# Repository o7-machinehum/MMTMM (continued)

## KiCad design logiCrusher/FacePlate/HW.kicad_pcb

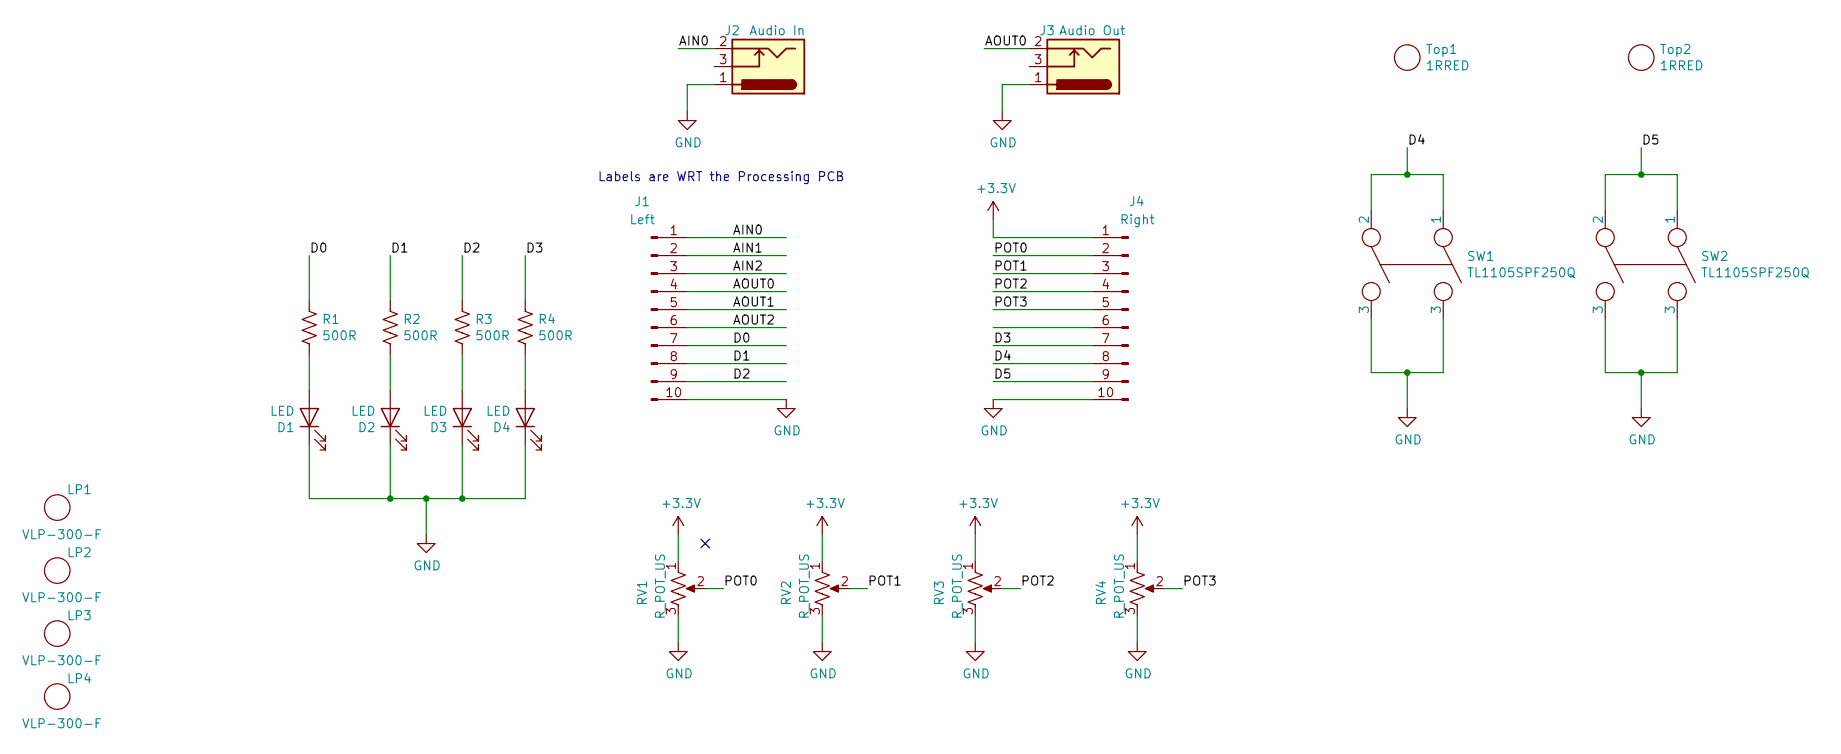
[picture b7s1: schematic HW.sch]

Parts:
D1, D2, D3, D4: LED; LED_0805_2012Metric
J1: Left; PinHeader_1x10_P2.54mm_Vertical
J2: Audio In; PJ301M-12
J3: Audio Out; PJ301M-12
J4: Right; PinHeader_1x10_P2.54mm_Vertical
LP1, LP2, LP3, LP4: VLP-300-F
R1, R2, R3, R4: 500R; R_0805_2012Metric
RV1, RV2, RV3, RV4: R_POT_US; Alpha9mmPot
SW1, SW2: TL1105SPF250Q
Top1, Top2: 1RRED

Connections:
+3V3: J4.1, RV1.1, RV2.1, RV3.1, RV4.1
/AIN0: J1.1, J2.2
/AIN1: J1.2
/AIN2: J1.3
/AOUT0: J1.4, J3.2
/AOUT1: J1.5
/AOUT2: J1.6
/D0: J1.7, R1.1
/D1: J1.8, R2.1
/D2: J1.9, R3.1
/D3: J4.7, R4.1
/D4: J4.8, SW1.1, SW1.2
/D5: J4.9, SW2.1, SW2.2
/POT0: J4.2, RV1.2
/POT1: J4.3, RV2.2
/POT2: J4.4, RV3.2
/POT3: J4.5, RV4.2
GND: D1.1 (K), D2.1 (K), D3.1 (K), D4.1 (K), J1.10, J2.1, J3.1, J4.10, RV1.3, RV2.3, RV3.3, RV4.3, SW1.3, SW2.3
unnamed: D1.2 (A), R1.2
unnamed: D2.2 (A), R2.2
unnamed: D3.2 (A), R3.2
unnamed: D4.2 (A), R4.2

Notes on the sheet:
Labels are WRT the Processing PCB

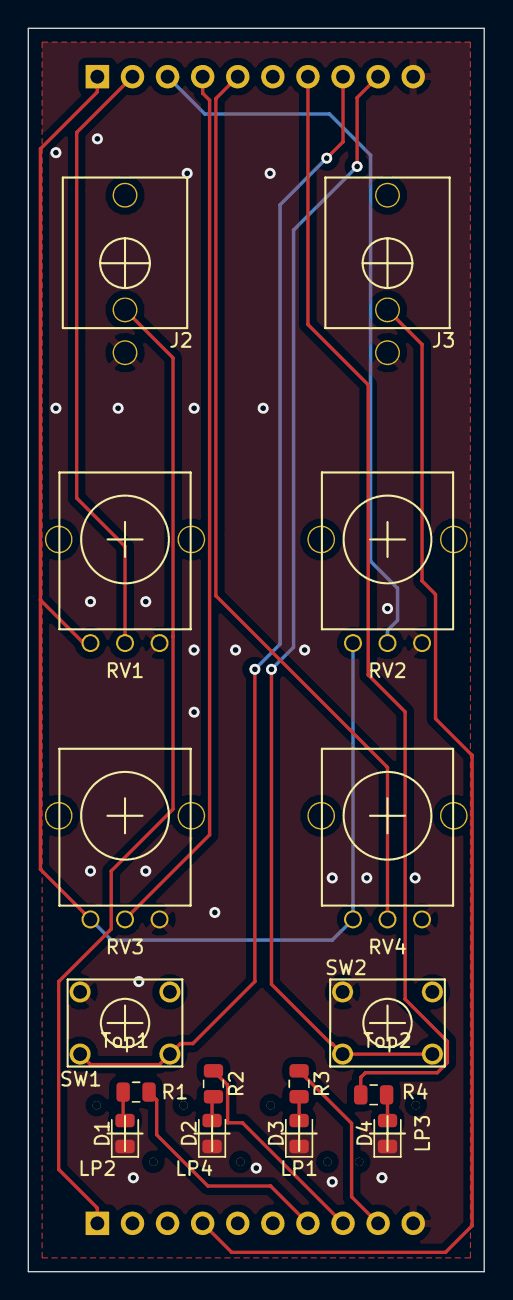
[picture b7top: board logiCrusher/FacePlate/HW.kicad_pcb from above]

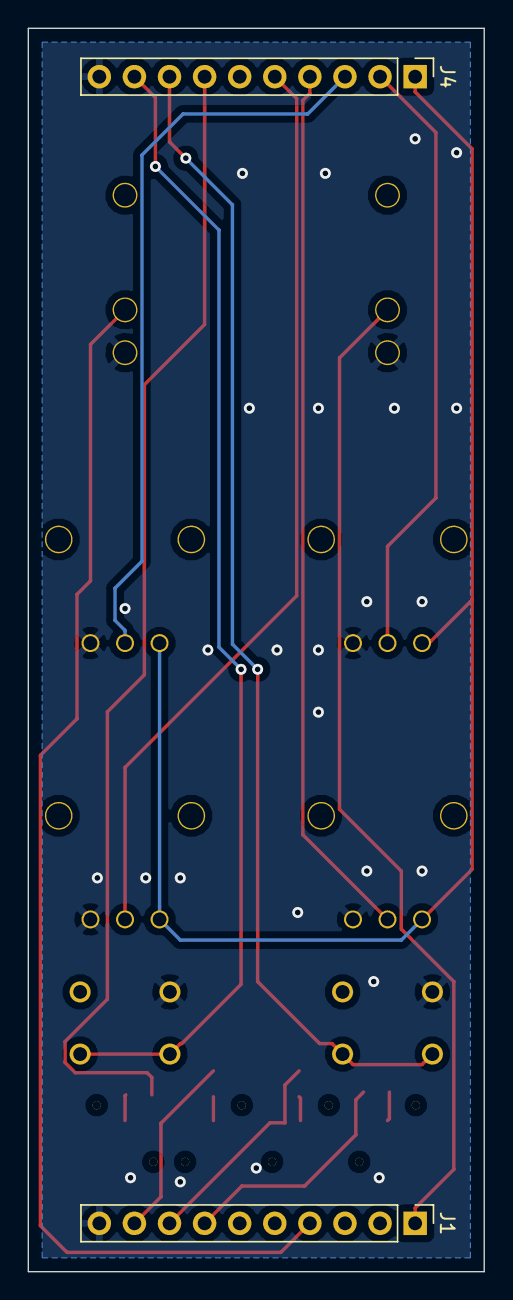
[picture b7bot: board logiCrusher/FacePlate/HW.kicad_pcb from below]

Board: 2 copper layers, 33.0 x 90.0 mm, 24 parts (2 on the bottom side), 18 nets.

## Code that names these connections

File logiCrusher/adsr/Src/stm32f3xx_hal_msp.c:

#include "main.h"
extern DMA_HandleTypeDef hdma_adc1;
void HAL_MspInit(void)
{
  /* USER CODE BEGIN MspInit 0 */

  /* USER CODE END MspInit 0 */

  __HAL_RCC_SYSCFG_CLK_ENABLE();
  __HAL_RCC_PWR_CLK_ENABLE();

  /* System interrupt init*/
  /* PendSV_IRQn interrupt configuration */
  HAL_NVIC_SetPriority(PendSV_IRQn, 15, 0);

  /* USER CODE BEGIN MspInit 1 */

  /* USER CODE END MspInit 1 */
}

/**
* @brief ADC MSP Initialization
* This function configures the hardware resources used in this example
* @param hadc: ADC handle pointer
* @retval None
*/
void HAL_ADC_MspInit(ADC_HandleTypeDef* hadc)
{
  GPIO_InitTypeDef GPIO_InitStruct = {0};
  if(hadc->Instance==ADC1)
  {
  /* USER CODE BEGIN ADC1_MspInit 0 */

  /* USER CODE END ADC1_MspInit 0 */
    /* Peripheral clock enable */
    __HAL_RCC_ADC1_CLK_ENABLE();
  
    __HAL_RCC_GPIOA_CLK_ENABLE();
    /**ADC1 GPIO Configuration    
    PA0     ------> ADC1_IN0
    PA1     ------> ADC1_IN1
    PA2     ------> ADC1_IN2
    PA3     ------> ADC1_IN3 
    */
    GPIO_InitStruct.Pin = GPIO_PIN_0|GPIO_PIN_1|GPIO_PIN_2|GPIO_PIN_3;
    GPIO_InitStruct.Mode = GPIO_MODE_ANALOG;
    GPIO_InitStruct.Pull = GPIO_NOPULL;
    HAL_GPIO_Init(GPIOA, &GPIO_InitStruct);

  }

}

/**
* @brief ADC MSP De-Initialization
* This function freeze the hardware resources used in this example
* @param hadc: ADC handle pointer
* @retval None
*/
void HAL_ADC_MspDeInit(ADC_HandleTypeDef* hadc)
{
  if(hadc->Instance==ADC1)
  {
  /* USER CODE BEGIN ADC1_MspDeInit 0 */

  /* USER CODE END ADC1_MspDeInit 0 */
    /* Peripheral clock disable */
    __HAL_RCC_ADC1_CLK_DISABLE();
  
    /**ADC1 GPIO Configuration    
    PA0     ------> ADC1_IN0
    PA1     ------> ADC1_IN1
    PA2     ------> ADC1_IN2
    PA3     ------> ADC1_IN3 
    */
    HAL_GPIO_DeInit(GPIOA, GPIO_PIN_0|GPIO_PIN_1|GPIO_PIN_2|GPIO_PIN_3);

    /* ADC1 DMA DeInit */
    HAL_DMA_DeInit(hadc->DMA_Handle);
  /* USER CODE BEGIN ADC1_MspDeInit 1 */

  /* USER CODE END ADC1_MspDeInit 1 */
  }

}

/**
* @brief DAC MSP Initialization
* This function configures the hardware resources used in this example
* @param hdac: DAC handle pointer
* @retval None
*/
void HAL_DAC_MspInit(DAC_HandleTypeDef* hdac)
{
  GPIO_InitTypeDef GPIO_InitStruct = {0};
  if(hdac->Instance==DAC1)
  {
  /* USER CODE BEGIN DAC1_MspInit 0 */

  /* USER CODE END DAC1_MspInit 0 */
    /* Peripheral clock enable */
    __HAL_RCC_DAC1_CLK_ENABLE();
  
    __HAL_RCC_GPIOA_CLK_ENABLE();
    /**DAC1 GPIO Configuration    
    PA4     ------> DAC1_OUT1 
    */
    GPIO_InitStruct.Pin = GPIO_PIN_4;
    GPIO_InitStruct.Mode = GPIO_MODE_ANALOG;
    GPIO_InitStruct.Pull = GPIO_NOPULL;
    HAL_GPIO_Init(GPIOA, &GPIO_InitStruct);

  /* USER CODE BEGIN DAC1_MspInit 1 */

  /* USER CODE END DAC1_MspInit 1 */
  }
  else if(hdac->Instance==DAC2)
  {
  /* USER CODE BEGIN DAC2_MspInit 0 */

  /* USER CODE END DAC2_MspInit 0 */
    /* Peripheral clock enable */
    __HAL_RCC_DAC2_CLK_ENABLE();
  
    __HAL_RCC_GPIOA_CLK_ENABLE();
    /**DAC2 GPIO Configuration    
    PA6     ------> DAC2_OUT1 
    */
    GPIO_InitStruct.Pin = GPIO_PIN_6;
    GPIO_InitStruct.Mode = GPIO_MODE_ANALOG;
    GPIO_InitStruct.Pull = GPIO_NOPULL;
    HAL_GPIO_Init(GPIOA, &GPIO_InitStruct);

  /* USER CODE BEGIN DAC2_MspInit 1 */

  /* USER CODE END DAC2_MspInit 1 */
  }

}

/**
* @brief DAC MSP De-Initialization
* This function freeze the hardware resources used in this example
* @param hdac: DAC handle pointer
* @retval None
*/
void HAL_DAC_MspDeInit(DAC_HandleTypeDef* hdac)
{
  if(hdac->Instance==DAC1)
  {
  /* USER CODE BEGIN DAC1_MspDeInit 0 */

  /* USER CODE END DAC1_MspDeInit 0 */
    /* Peripheral clock disable */
    __HAL_RCC_DAC1_CLK_DISABLE();
  
    /**DAC1 GPIO Configuration    
    PA4     ------> DAC1_OUT1 
    */
    HAL_GPIO_DeInit(GPIOA, GPIO_PIN_4);

  /* USER CODE BEGIN DAC1_MspDeInit 1 */

  /* USER CODE END DAC1_MspDeInit 1 */
  }
  else if(hdac->Instance==DAC2)
  {
  /* USER CODE BEGIN DAC2_MspDeInit 0 */

  /* USER CODE END DAC2_MspDeInit 0 */
    /* Peripheral clock disable */
    __HAL_RCC_DAC2_CLK_DISABLE();
  
    /**DAC2 GPIO Configuration    
    PA6     ------> DAC2_OUT1 
    */
    HAL_GPIO_DeInit(GPIOA, GPIO_PIN_6);

  /* USER CODE BEGIN DAC2_MspDeInit 1 */

  /* USER CODE END DAC2_MspDeInit 1 */
  }

}

/**
* @brief SDADC MSP Initialization
* This function configures the hardware resources used in this example
* @param hsdadc: SDADC handle pointer
* @retval None
*/
void HAL_SDADC_MspInit(SDADC_HandleTypeDef* hsdadc)
{
  GPIO_InitTypeDef GPIO_InitStruct = {0};
  if(hsdadc->Instance==SDADC1)
  {
    /* Peripheral clock enable */
    __HAL_RCC_SDADC1_CLK_ENABLE();
    __HAL_RCC_GPIOB_CLK_ENABLE();
    /**SDADC1 GPIO Configuration    
    PB2     ------> SDADC1_AIN4P 
    */
    GPIO_InitStruct.Pin = GPIO_PIN_2;
    GPIO_InitStruct.Mode = GPIO_MODE_ANALOG;
    GPIO_InitStruct.Pull = GPIO_NOPULL;
    HAL_GPIO_Init(GPIOB, &GPIO_InitStruct);
    
    HAL_NVIC_SetPriority(SDADC1_IRQn, 5, 0);
    HAL_NVIC_EnableIRQ(SDADC1_IRQn);
  }
}

/**
* @brief SDADC MSP De-Initialization
* This function freeze the hardware resources used in this example
* @param hsdadc: SDADC handle pointer
* @retval None
*/
void HAL_SDADC_MspDeInit(SDADC_HandleTypeDef* hsdadc)
{
  if(hsdadc->Instance==SDADC1)
  {
  /* USER CODE BEGIN SDADC1_MspDeInit 0 */

  /* USER CODE END SDADC1_MspDeInit 0 */
    /* Peripheral clock disable */
    __HAL_RCC_SDADC1_CLK_DISABLE();
  
    /**SDADC1 GPIO Configuration    
    PB2     ------> SDADC1_AIN4P 
    */
    HAL_GPIO_DeInit(GPIOB, GPIO_PIN_2);

  /* USER CODE BEGIN SDADC1_MspDeInit 1 */

  /* USER CODE END SDADC1_MspDeInit 1 */
  }

}

/**
* @brief UART MSP Initialization
* This function configures the hardware resources used in this example
* @param huart: UART handle pointer
* @retval None
*/
void HAL_UART_MspInit(UART_HandleTypeDef* huart)
{
  GPIO_InitTypeDef GPIO_InitStruct = {0};
  if(huart->Instance==USART2)
  {
  /* USER CODE BEGIN USART2_MspInit 0 */

  /* USER CODE END USART2_MspInit 0 */
    /* Peripheral clock enable */
    __HAL_RCC_USART2_CLK_ENABLE();
  
    __HAL_RCC_GPIOB_CLK_ENABLE();
    /**USART2 GPIO Configuration    
    PB3     ------> USART2_TX
    PB4     ------> USART2_RX 
    */
    GPIO_InitStruct.Pin = GPIO_PIN_3|GPIO_PIN_4;
    GPIO_InitStruct.Mode = GPIO_MODE_AF_PP;
    GPIO_InitStruct.Pull = GPIO_NOPULL;
    GPIO_InitStruct.Speed = GPIO_SPEED_FREQ_HIGH;
    GPIO_InitStruct.Alternate = GPIO_AF7_USART2;
    HAL_GPIO_Init(GPIOB, &GPIO_InitStruct);

    /* USART2 interrupt Init */
    HAL_NVIC_SetPriority(USART2_IRQn, 5, 0);
    HAL_NVIC_EnableIRQ(USART2_IRQn);
  /* USER CODE BEGIN USART2_MspInit 1 */

  /* USER CODE END USART2_MspInit 1 */
  }

}

/**
* @brief UART MSP De-Initialization
* This function freeze the hardware resources used in this example
* @param huart: UART handle pointer
* @retval None
*/
void HAL_UART_MspDeInit(UART_HandleTypeDef* huart)
{
  if(huart->Instance==USART2)
  {
  /* USER CODE BEGIN USART2_MspDeInit 0 */

  /* USER CODE END USART2_MspDeInit 0 */
    /* Peripheral clock disable */
    __HAL_RCC_USART2_CLK_DISABLE();
  
    /**USART2 GPIO Configuration    
    PB3     ------> USART2_TX
    PB4     ------> USART2_RX 
    */
    HAL_GPIO_DeInit(GPIOB, GPIO_PIN_3|GPIO_PIN_4);

    /* USART2 interrupt DeInit */
    HAL_NVIC_DisableIRQ(USART2_IRQn);
  /* USER CODE BEGIN USART2_MspDeInit 1 */

  /* USER CODE END USART2_MspDeInit 1 */
  }

}

/* USER CODE BEGIN 1 */

/* USER CODE END 1 */

/************************ (C) COPYRIGHT STMicroelectronics *****END OF FILE****/

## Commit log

2018-09-25 init
2018-09-25 Added kicad files for VCO front plate.
2018-10-03 Updated the readme
2018-11-07 Added Altium files for front plate.
2018-11-08 Renders done for VCO front plate.
2018-11-09 Added front files for for LFO
2018-12-04 Changed the readme
2018-12-25 Cleaned up the spec for VCM
2018-12-25 Typo
2018-12-25 Added some parts
2018-12-25 Added some notes in the spec
2018-12-27 Added another MCU
2018-12-27 Added some kicad files
2018-12-27 Added power headers and some caps for the pcb.
2018-12-29 Moved some shit around, changed the spec, worked on the PCB
2019-01-03 Worked on the PCB
2019-01-04 Routed some of the lines in.
2019-01-08 Added buffer parts
2019-02-28 Finished the first crack at the drum module
2019-03-08 Finished ASDR schematic.
2019-03-24 Made FW for the logiCrusher
2019-03-24 Going to generate cube stuff
2019-03-24 Added required handle
2019-03-24 Did not get the PWM working yet
2019-03-26 Worked on the Drum
2019-03-28 Organized layout of drum, should be ready for routing.
2019-03-30 Moved the logicCrusher to an f3
2019-04-06 worked on the layout of the drum
2019-04-11 Finished off the drum
2019-04-11 Worked on the readme
2019-04-11 Small readme change
2019-04-11 readme
2019-04-11 Removed ASDR HW and moved it to the logic crusher
2019-04-12 Added the front plate files
2019-04-15 Finished the IO module
2019-04-16 Worked on the HW for the mcu module
2019-04-22 Added a switching regulator
2019-04-22 Removed submodules
2019-04-22 Added some deps
2019-04-22 Got the 3d stuff worked out.
2019-04-23 Moved some shit around
2019-04-23 Worked on the layout for the logicrusher
2019-04-23 Spend a lot of time working on the logicCrusher HW
2019-04-25 Generated build files
2019-04-25 Renamed files
2019-04-25 Added faceplate output
2019-04-25 Made fabrication files
2019-04-25 IO faceplate added for the drum
2019-04-25 Added step file for the drum
2019-05-20 Fit check on the drum and logiccrusher
2019-05-23 Added simulation files and fixed the values of the gain resistors.
2019-06-19 Added the bom for the drum
2019-06-22 Added some filter calculations
2019-06-22 locked in filter values
2019-06-22 Forgot to save
2019-06-28 Thanks Walker
2019-07-09 Plotted the drum
2019-07-11 Added and verified most of the calculations.
2019-07-12 20190711 PDF schematic export
2019-07-12 Deleted derekwashere.txt (but he's still here)
2019-07-12 Added some math
2019-07-14 Added some notes on the drum
2019-07-15 Added a new dir specifically for the adsr project. There were also a bunch of gerber files that had positive diffs... That's not good :(
2019-07-15 pushing those gerbs I was refering to in the last commit
2019-07-15 reup reup
2019-07-16 Callback still not working
2019-07-22 y = x working
2019-07-22 Removed stuff for the old adc (This needs to come back later for the knobs.
2019-07-25 Added files for the manual
2019-08-02 Added some files and updated the manual
2019-08-13 y = x working now.
2019-08-27 Made some changes to the asdr class.
2019-09-01 adsr working, need to implement the actual adsr knobs.
2019-09-09 Worked on the adsr
2019-10-10 Changes to the README
2019-10-12 Updated readme and removed an old project.
2019-10-14 Added DMA to normal ADC, not tested
2019-10-14 Noting
2019-10-14 Enables the DMA channel and made changes to main
2019-10-14 Getting HAL_ADC_ConvCpltCallback callback, however it only happens once and only the first two bytes are filled w/ data.
2019-10-16 Trying to get the sdadc working
2019-10-17 Finally got the fucking thing working lol
2019-10-18 Added a readme for the logiccrusher.
2020-01-14 added gerbers for the faceplate
2020-01-17 Bunch of uncommited crap, no idea what it is lol
2020-01-18 Updated parts for the Bob bass
